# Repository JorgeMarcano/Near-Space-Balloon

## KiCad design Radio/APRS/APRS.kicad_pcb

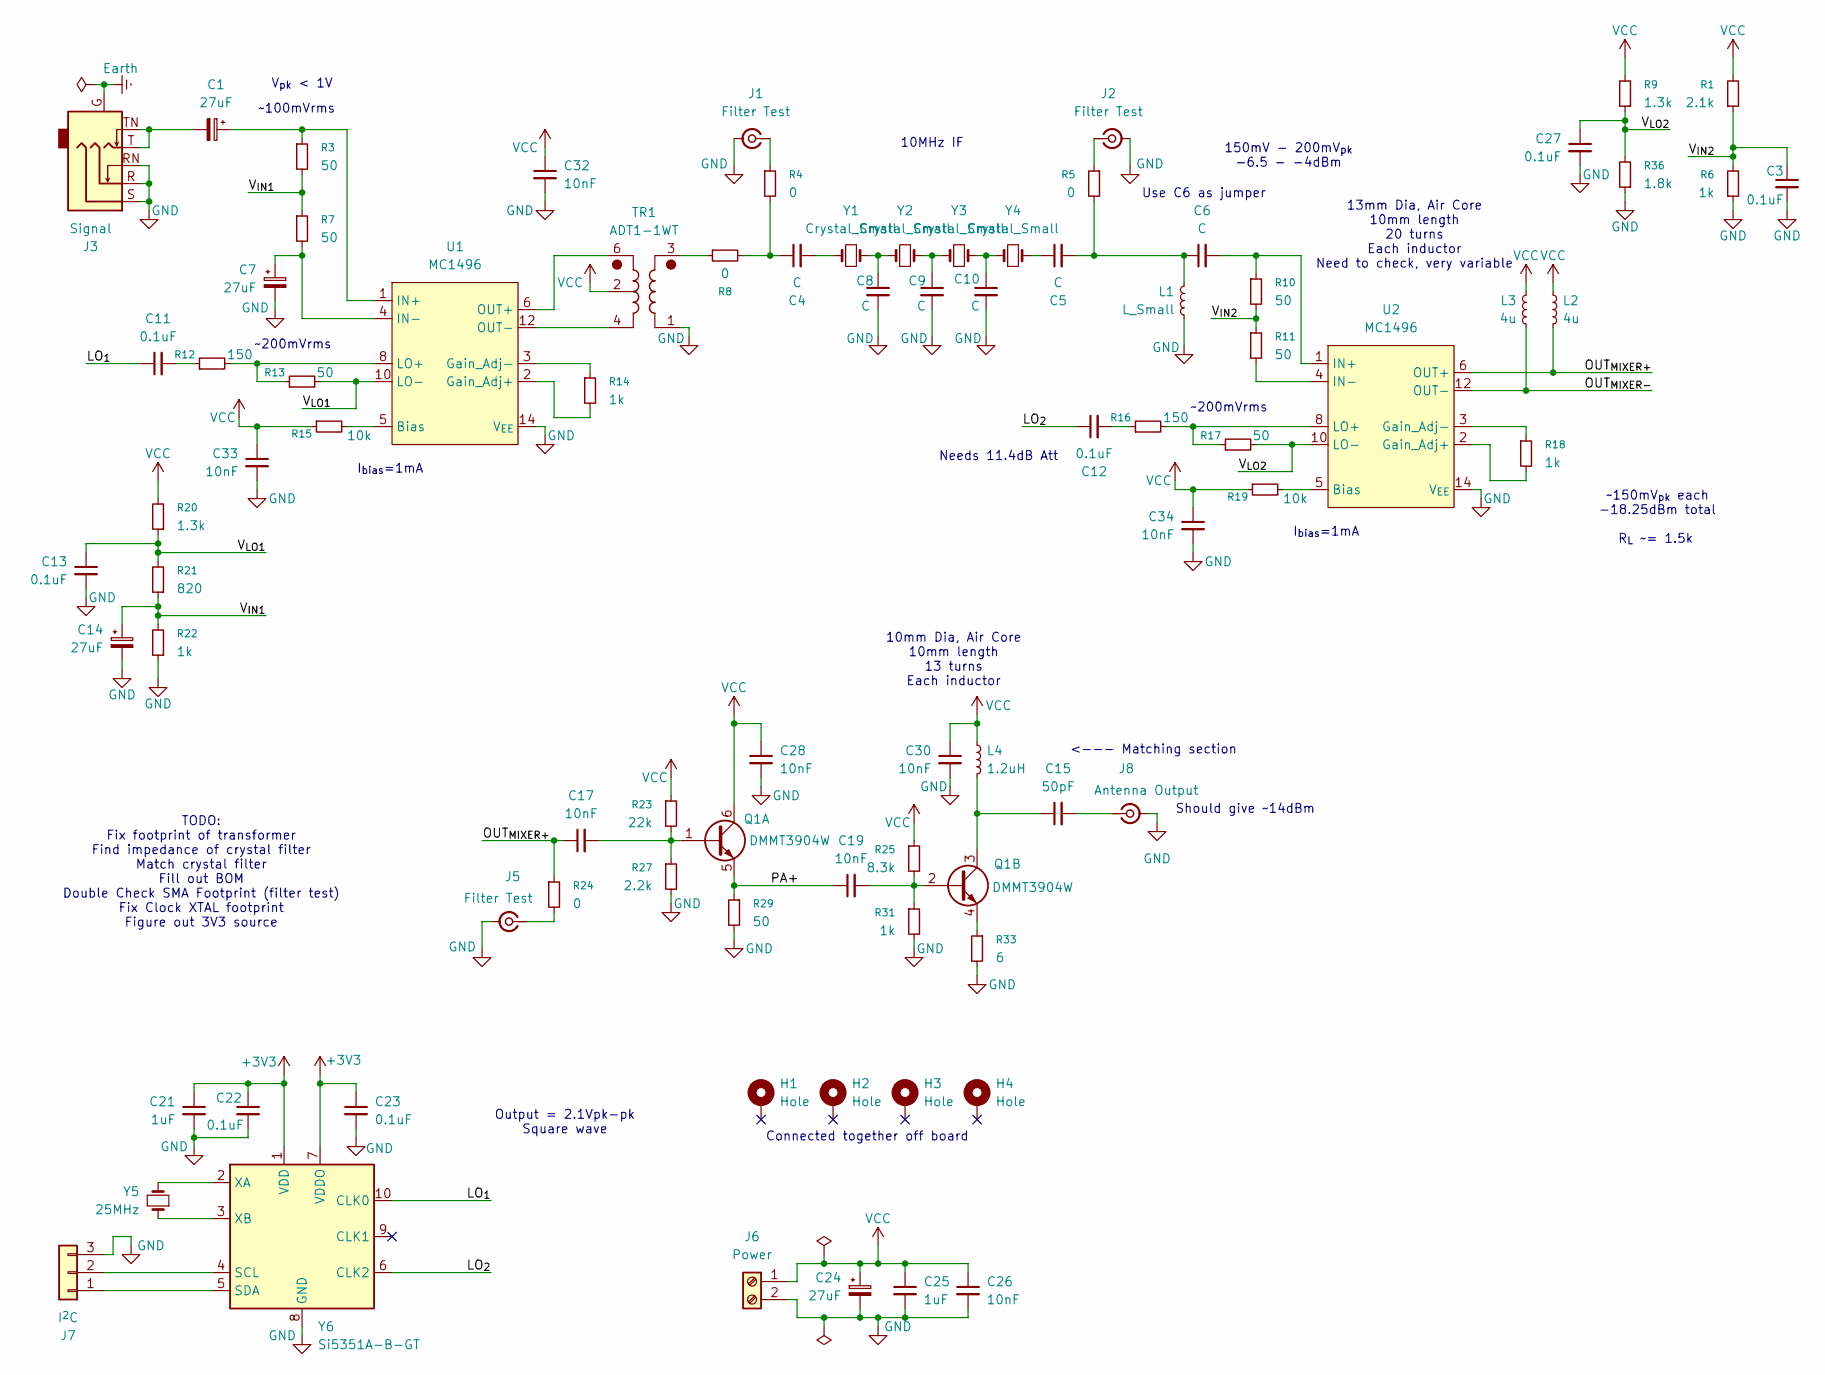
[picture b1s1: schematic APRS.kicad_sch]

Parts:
C1, C7, C14, C24: 27uF; CP_Radial_D6.3mm_P2.50mm; Digikey P/N 399-A7C0EN276M1JAAS060-ND
C3, C11, C12, C13, C22, C23, C27: 0.1uF; C_0603_1608Metric_Pad1.08x0.95mm_HandSolder; Digikey P/N 490-GRM3195C1H104JA05DCT-ND
C4, C5, C6, C8, C9, C10: C; C_0603_1608Metric_Pad1.08x0.95mm_HandSolder
C15: 50pF; C_0603_1608Metric_Pad1.08x0.95mm_HandSolder; Digikey P/N 1276-2310-1-ND
C17, C19, C26, C28, C30, C32, C33, C34: 10nF; C_0603_1608Metric_Pad1.08x0.95mm_HandSolder
C21, C25: 1uF; C_0603_1608Metric_Pad1.08x0.95mm_HandSolder
H1, H2, H3, H4: Hole; MountingHole_2.2mm_M2_ISO14580_Pad
J1, J2, J5: Filter Test; SMA_Molex_73251-1153_EdgeMount_Horizontal
J3: Signal; Jack_3.5mm; Digikey P/N 1939-G-1362-ND
J6: Power; PinHeader_1x02_P2.54mm_Vertical
J7: I^{2}C; PinHeader_1x03_P2.54mm_Vertical
J8: Antenna Output; SMA_Molex_73251-1153_EdgeMount_Horizontal
L1: L_Small; Inductor_P15.24mm_Horizontal
L2, L3: 4u; Inductor_P15.24mm_Horizontal
L4: 1.2uH; Inductor_P15.24mm_Horizontal
Q1: DMMT3904W; SOT-363_SC-70-6; Digikey P/N DMMT3904W-FDICT-ND
R1: 2.1k; R_0603_1608Metric_Pad0.98x0.95mm_HandSolder
R3, R7, R10, R11, R13, R17, R29: 50; R_0603_1608Metric_Pad0.98x0.95mm_HandSolder
R4, R5, R8, R24: 0; R_0603_1608Metric_Pad0.98x0.95mm_HandSolder
R6, R14, R18, R22, R31: 1k; R_0603_1608Metric_Pad0.98x0.95mm_HandSolder
R9, R20: 1.3k; R_0603_1608Metric_Pad0.98x0.95mm_HandSolder
R12, R16: 150; R_0603_1608Metric_Pad0.98x0.95mm_HandSolder
R15, R19: 10k; R_0603_1608Metric_Pad0.98x0.95mm_HandSolder
R21: 820; R_0603_1608Metric_Pad0.98x0.95mm_HandSolder
R23: 22k; R_0603_1608Metric_Pad0.98x0.95mm_HandSolder
R25: 8.3k; R_0603_1608Metric_Pad0.98x0.95mm_HandSolder
R27: 2.2k; R_0603_1608Metric_Pad0.98x0.95mm_HandSolder
R33: 6; R_0603_1608Metric_Pad0.98x0.95mm_HandSolder
R36: 1.8k; R_0603_1608Metric_Pad0.98x0.95mm_HandSolder
TR1: ADT1-1WT; Mini-Circuits_CD542_H2.84mm
U1, U2: MC1496; SOIC-14_3.9x8.7mm_P1.27mm; Digikey P/N MC1496BDR2GOSCT-ND
Y1, Y2, Y3, Y4: Crystal_Small; Crystal_HC18-U_Vertical
Y5: 25MHz; Crystal_SMD_0603-4Pin_6.0x3.5mm_HandSoldering
Y6: Si5351A-B-GT; MSOP-10_3x3mm_P0.5mm; Digikey P/N 336-3908-1-ND

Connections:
+3V3: C21.1, C22.1, C23.1, Y6.1 (VDD), Y6.7 (VDDO)
/LO_{1}: C11.1, Y6.10 (CLK0)
/LO_{2}: C12.1, Y6.6 (CLK2)
/OUT_{MIXER+}: C17.1, L2.2, R24.1, U2.6 (OUT+)
/OUT_{MIXER-}: L3.2, U2.12 (OUT-)
/PA+: C19.1, Q1.5 (E1), R29.1
/V_{IN1}: C14.1, R3.2, R7.1, R21.1, R22.2
/V_{IN2}: C3.1, R1.1, R6.2, R10.2, R11.1
/V_{LO1}: C13.1, R13.2, R20.1, R21.2, U1.10 (LO-)
/V_{LO2}: C27.1, R9.1, R17.2, R36.2, U2.10 (LO-)
GND: C3.2, C7.2, C8.2, C9.2, C10.2, C13.2, C14.2, C21.2, C22.2, C23.2, C24.2, C25.2, C26.2, C27.2, C28.2, C30.2, C32.2, C33.2, C34.2, J1.2 (Ext), J2.2 (Ext), J3.R, J3.RN, J3.S, J5.2 (Ext), J6.2, J7.3, J8.2 (Ext), L1.2, R6.1, R22.1, R27.2, R29.2, R31.2, R33.2, R36.1, TR1.1, U1.14 (V_{EE}), U2.14 (V_{EE}), Y6.8 (GND)
unnamed: C1.2, J3.T, J3.TN
unnamed: C4.1, R4.2, R8.2
unnamed: C4.2, Y1.1
unnamed: C5.1, Y4.2
unnamed: C5.2, C6.1, L1.1, R5.2
unnamed: C8.1, Y1.2, Y2.1
unnamed: C9.1, Y2.2, Y3.1
unnamed: C10.1, Y3.2, Y4.1
unnamed: C11.2, R12.1
unnamed: C12.2, R16.1
unnamed: J1.1 (In), R4.1
unnamed: J2.1 (In), R5.1
unnamed: J5.1 (In), R24.2
unnamed: J7.1, Y6.5 (SDA)
unnamed: J7.2, Y6.4 (SCL)
unnamed: C15.2, J8.1 (In)
unnamed: C17.2, Q1.1 (B1), R23.2, R27.1
unnamed: C19.2, Q1.2 (B2), R25.2, R31.1
unnamed: C15.1, L4.2, Q1.3 (C2)
unnamed: Q1.4 (E2), R33.1
unnamed: R8.1, TR1.3
unnamed: R15.2, U1.5 (Bias)
unnamed: R14.2, U1.2 (Gain_Adj+)
unnamed: R14.1, U1.3 (Gain_Adj-)
unnamed: C1.1, R3.1, U1.1 (IN+)
unnamed: C7.1, R7.2, U1.4 (IN-)
unnamed: R12.2, R13.1, U1.8 (LO+)
unnamed: TR1.6, U1.6 (OUT+)
unnamed: TR1.4, U1.12 (OUT-)
unnamed: R19.2, U2.5 (Bias)
unnamed: R18.2, U2.2 (Gain_Adj+)
unnamed: R18.1, U2.3 (Gain_Adj-)
unnamed: C6.2, R10.1, U2.1 (IN+)
unnamed: R11.2, U2.4 (IN-)
unnamed: R16.2, R17.1, U2.8 (LO+)
unnamed: Y5.2, Y6.2 (XA)
unnamed: Y5.1, Y6.3 (XB)
VCC: C24.1, C25.1, C26.1, C28.1, C30.1, C32.1, C33.1, C34.1, J6.1, L2.1, L3.1, L4.1, Q1.6 (C1), R1.2, R9.2, R15.1, R19.1, R20.2, R23.1, R25.1, TR1.2

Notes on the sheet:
<--- Matching section
~100mVrms
10mm Dia, Air Core 10mm length 13 turns Each inductor
~150mV_{pk} each -18.25dBm total
Should give ~14dBm
~200mVrms
13mm Dia, Air Core 10mm length 20 turns Each inductor Need to check, very variable
10MHz IF
150mV - 200mV_{pk} -6.5 - -4dBm
R_{L} ~= 1.5k
I_{bias}=1mA
Connected together off board
V_{pk} < 1V
TODO: Fix footprint of transformer Find impedance of crystal filter Match crystal filter Fill out BOM Double Check SMA Footprint (filter test) Fix Clock XTAL footprint Figure out 3V3 source
Output = 2.1Vpk-pk Square wave
Needs 11.4dB Att
Use C6 as jumper

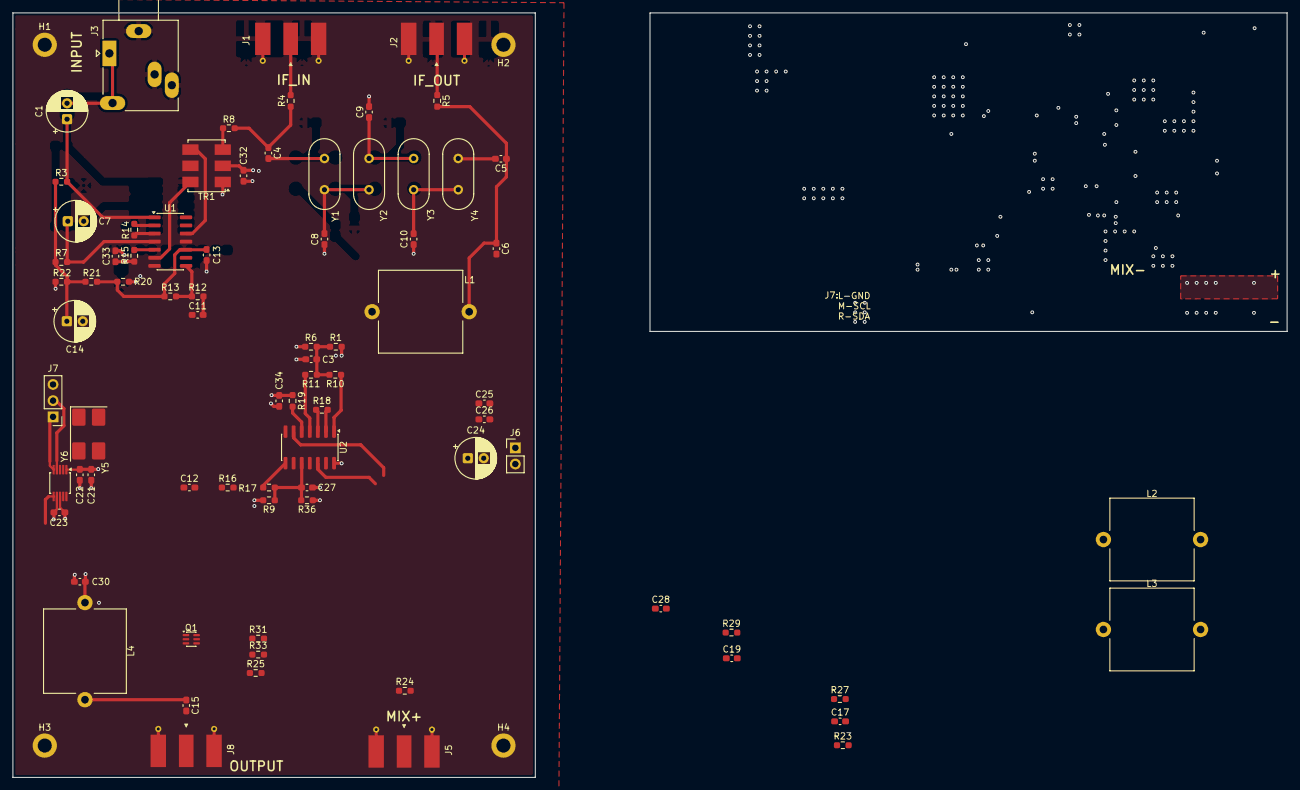
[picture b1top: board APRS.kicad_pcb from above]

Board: 4 copper layers, 82.0 x 120.0 mm, 82 parts (0 on the bottom side), 49 nets.

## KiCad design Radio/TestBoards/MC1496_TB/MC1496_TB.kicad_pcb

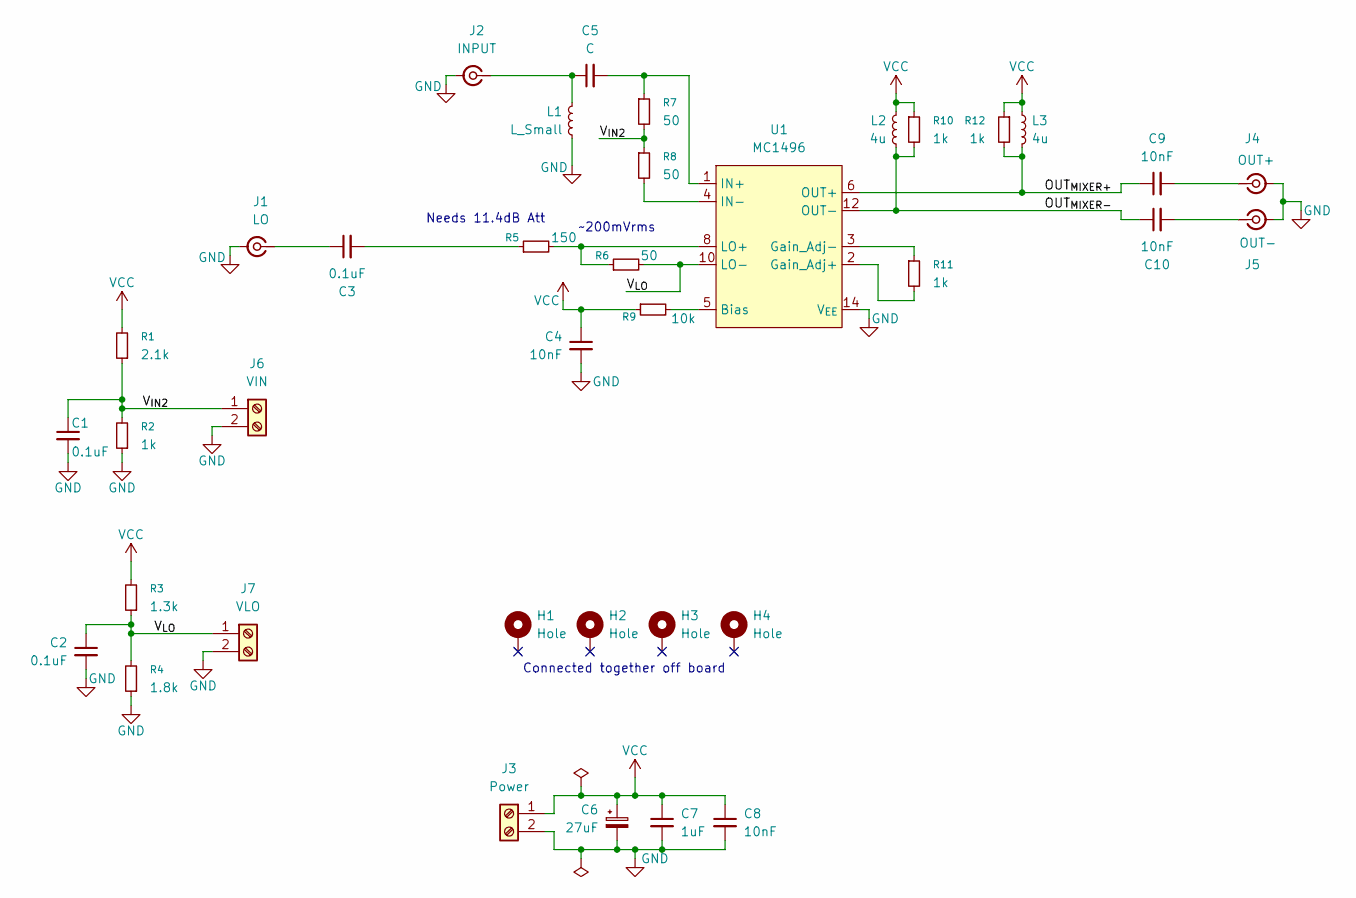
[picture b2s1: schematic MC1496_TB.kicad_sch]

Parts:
C1, C2, C3: 0.1uF; C_0603_1608Metric_Pad1.08x0.95mm_HandSolder; Digikey P/N 490-GRM3195C1H104JA05DCT-ND
C4, C8, C9, C10: 10nF; C_0603_1608Metric_Pad1.08x0.95mm_HandSolder
C5: C; C_0603_1608Metric_Pad1.08x0.95mm_HandSolder
C6: 27uF; CP_Radial_D6.3mm_P2.50mm; Digikey P/N 399-A7C0EN276M1JAAS060-ND
C7: 1uF; C_0603_1608Metric_Pad1.08x0.95mm_HandSolder
H1, H2, H3, H4: Hole; MountingHole_2.2mm_M2_ISO14580_Pad
J1: LO; SMA_Molex_73251-1153_EdgeMount_Horizontal
J2: INPUT; SMA_Molex_73251-1153_EdgeMount_Horizontal
J3: Power; PinHeader_1x02_P2.54mm_Vertical
J4: OUT+; SMA_Molex_73251-1153_EdgeMount_Horizontal
J5: OUT-; SMA_Molex_73251-1153_EdgeMount_Horizontal
J6: VIN; PinHeader_1x02_P2.54mm_Vertical
J7: VLO; PinHeader_1x02_P2.54mm_Vertical
L1: L_Small; Inductor_P15.24mm_Horizontal
L2, L3: 4u; Inductor_P15.24mm_Horizontal
R1: 2.1k; R_0603_1608Metric_Pad0.98x0.95mm_HandSolder
R2, R10, R11, R12: 1k; R_0603_1608Metric_Pad0.98x0.95mm_HandSolder
R3: 1.3k; R_0603_1608Metric_Pad0.98x0.95mm_HandSolder
R4: 1.8k; R_0603_1608Metric_Pad0.98x0.95mm_HandSolder
R5: 150; R_0603_1608Metric_Pad0.98x0.95mm_HandSolder
R6, R7, R8: 50; R_0603_1608Metric_Pad0.98x0.95mm_HandSolder
R9: 10k; R_0603_1608Metric_Pad0.98x0.95mm_HandSolder
U1: MC1496; SOIC-14_3.9x8.7mm_P1.27mm

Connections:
/OUT_{MIXER+}: C9.1, L3.2, R12.2, U1.6 (OUT+)
/OUT_{MIXER-}: C10.1, L2.2, R10.2, U1.12 (OUT-)
/V_{IN2}: C1.1, J6.1, R1.1, R2.2, R7.2, R8.1
/V_{LO}: C2.1, J7.1, R3.1, R4.2, R6.2, U1.10 (LO-)
GND: C1.2, C2.2, C4.2, C6.2, C7.2, C8.2, J1.2 (Ext), J2.2 (Ext), J3.2, J4.2 (Ext), J5.2 (Ext), J6.2, J7.2, L1.2, R2.1, R4.1, U1.14 (V_{EE})
unnamed: C3.2, R5.1
unnamed: C3.1, J1.1 (In)
unnamed: C5.1, J2.1 (In), L1.1
unnamed: C9.2, J4.1 (In)
unnamed: C10.2, J5.1 (In)
unnamed: R9.2, U1.5 (Bias)
unnamed: R11.2, U1.2 (Gain_Adj+)
unnamed: R11.1, U1.3 (Gain_Adj-)
unnamed: C5.2, R7.1, U1.1 (IN+)
unnamed: R8.2, U1.4 (IN-)
unnamed: R5.2, R6.1, U1.8 (LO+)
VCC: C4.1, C6.1, C7.1, C8.1, J3.1, L2.1, L3.1, R1.2, R3.2, R9.1, R10.1, R12.1

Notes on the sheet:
Needs 11.4dB Att
Connected together off board
~200mVrms

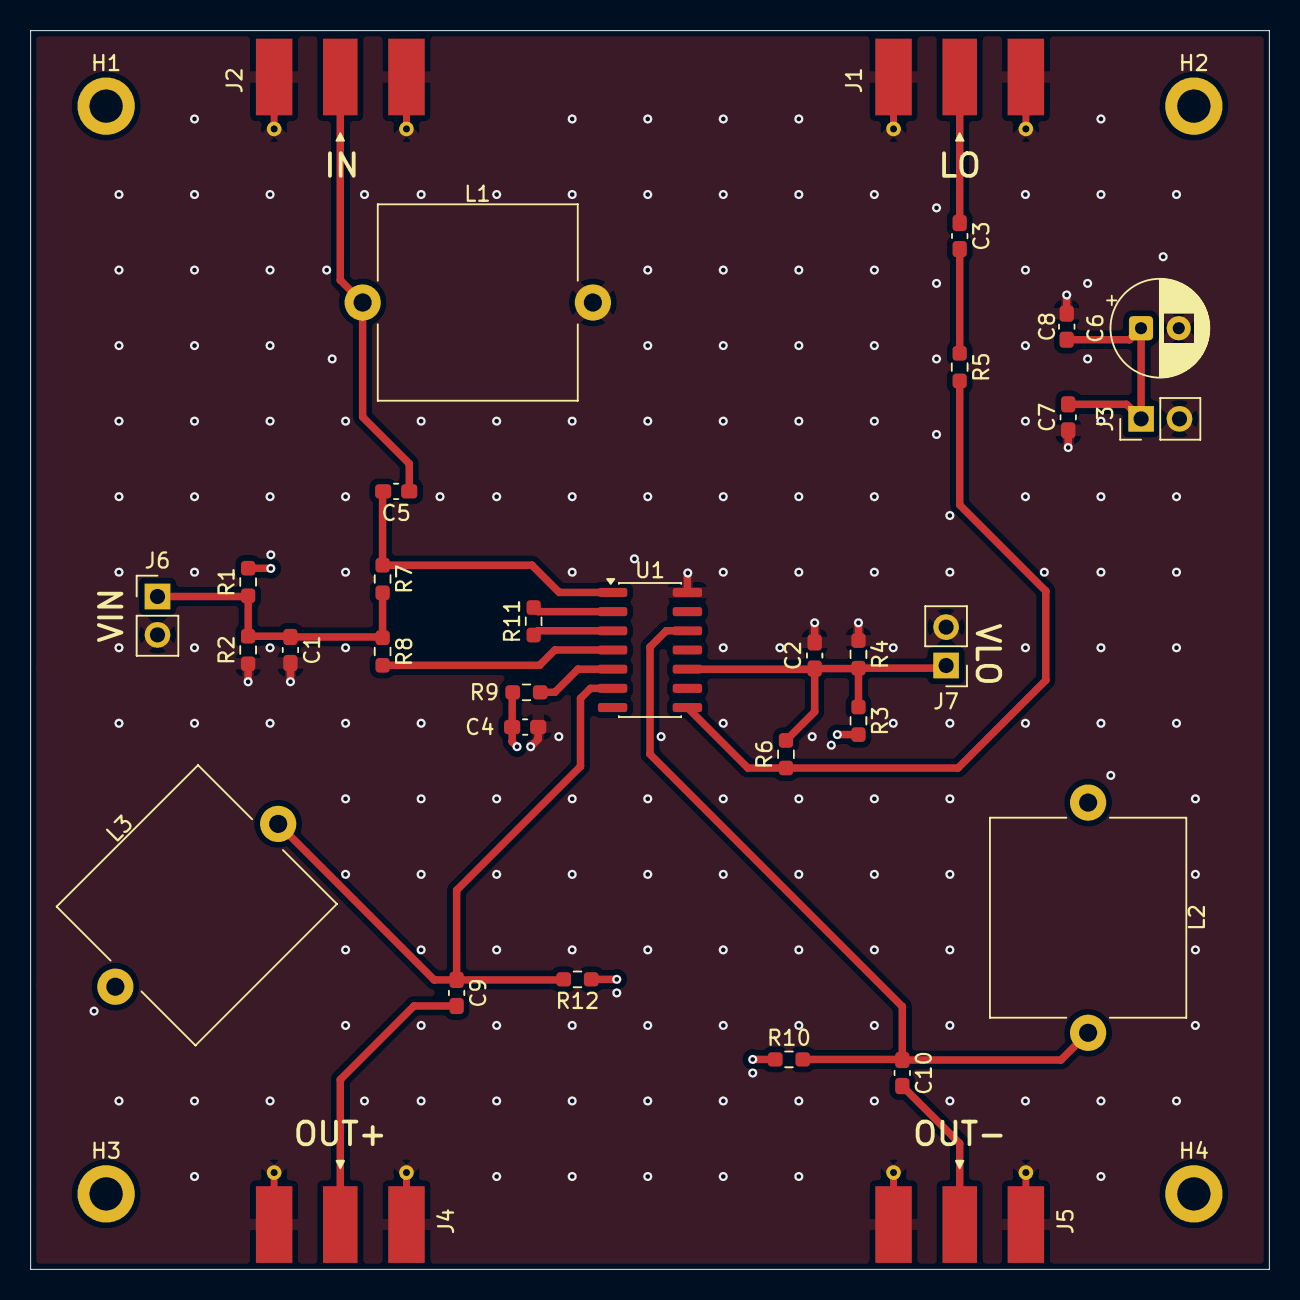
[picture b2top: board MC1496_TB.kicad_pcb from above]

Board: 4 copper layers, 82.0 x 82.0 mm, 37 parts (0 on the bottom side), 17 nets.
